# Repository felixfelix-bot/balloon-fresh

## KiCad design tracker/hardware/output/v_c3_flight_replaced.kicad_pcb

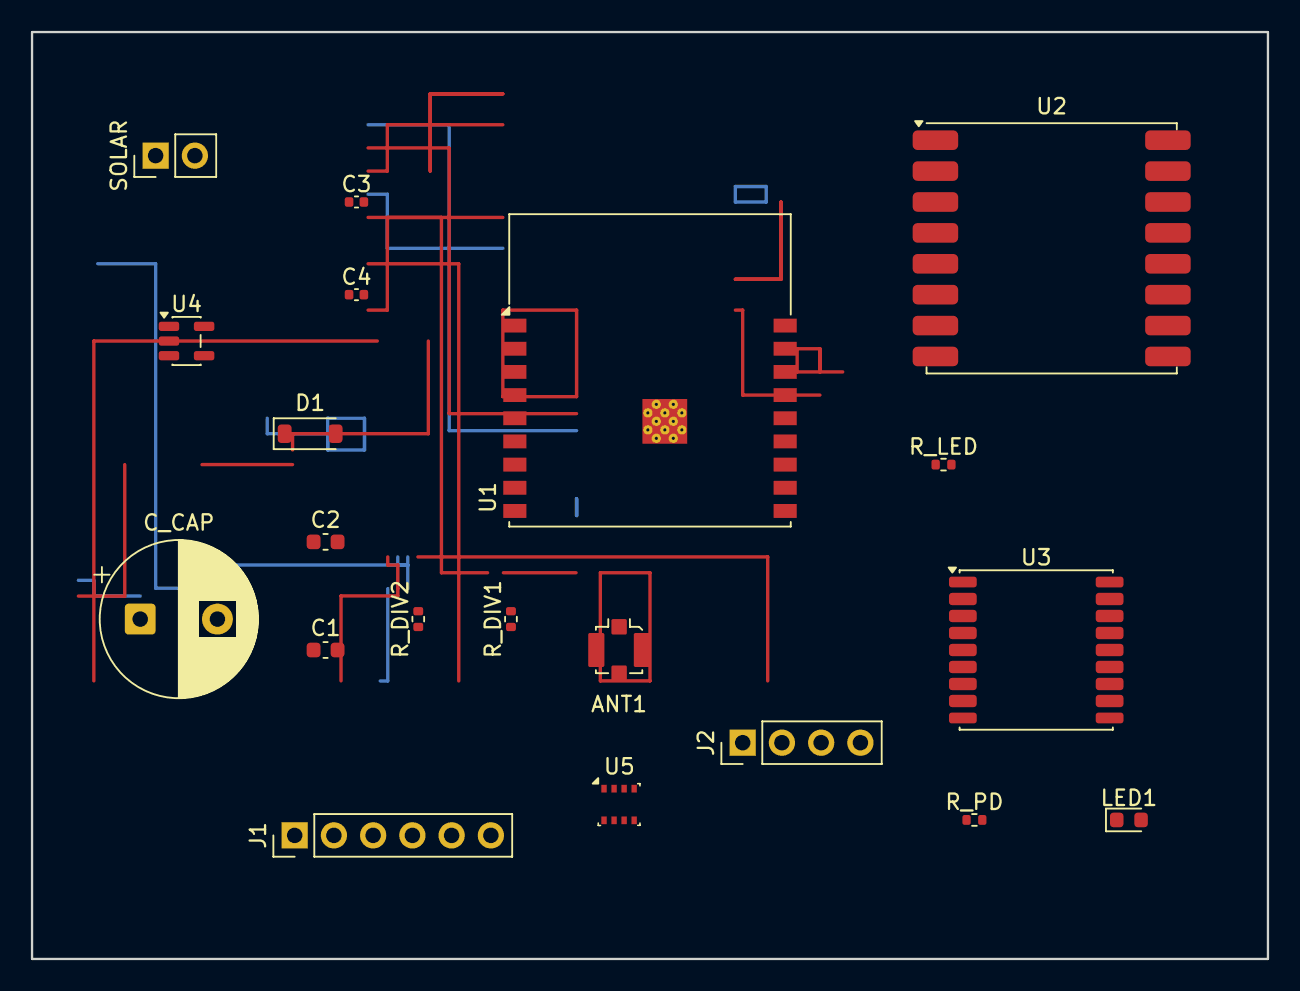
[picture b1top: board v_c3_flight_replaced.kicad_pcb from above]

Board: 4 copper layers, 80.0 x 60.0 mm, 20 parts (0 on the bottom side), 22 nets.

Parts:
ANT1: U.FL; U.FL_Molex_MCRF_73412-0110_Vertical
C1, C2: 10uF; C_0603_1608Metric
C3, C4: 100nF; C_0402_1005Metric
C_CAP: 1F_5.5V; CP_Radial_D10.0mm_P5.00mm
D1: BAT54; D_SOD-123
J1: Prog_Header; PinHeader_1x06_P2.54mm_Vertical
J2: Debug_Header; PinHeader_1x04_P2.54mm_Vertical
LED1: LED_RED; LED_0603_1608Metric
R_DIV1, R_DIV2: 100k; R_0402_1005Metric
R_LED: 330R; R_0402_1005Metric
R_PD: 10k; R_0402_1005Metric
SOLAR: Solar_In; PinHeader_1x02_P2.54mm_Vertical
U1: ESP32-C3-WROOM-02
U2: LR2021F33; HOPERF_RFM9XW_SMD
U3: MAX-M10S; ublox_MAX
U4: TPS7A02; SOT-23-5
U5: BMP280; Bosch_LGA-8_2.5x2.5mm_P0.65mm_ClockwisePinNumbering

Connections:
+3V3: C1.1, C2.1, C3.1, C4.1, J1.2, J2.2, R_PD.2, U1.1, U2.13, U3.7, U3.8, U4.5, U5.2, U5.6, U5.8
EN: J1.3, U1.2
GND: ANT1.2, C1.2, C2.2, C3.2, C4.2, C_CAP.2, J1.1, J2.1, LED1.2, R_DIV2.2, SOLAR.2, U1.9, U1.19, U2.1, U2.8, U2.10, U3.1, U3.10, U3.12, U4.2, U5.1, U5.5, U5.7
GPS_RX: U1.17, U3.2
GPS_TX: U1.18, U3.3
I2C_SCL: J2.4, U1.8, U5.4
I2C_SDA: J2.3, R_PD.1, U1.7, U5.3
LED_A: LED1.1, R_LED.2
LED_DRIVE: R_LED.1, U1.14
LR_BUSY: U1.3, U2.12
LR_DIO0: U1.13, U2.14
LR_RST: U1.15, U2.6
RF_OUT: ANT1.1, U2.9
SOLAR_IN: D1.1, SOLAR.1
SPI_MISO: U1.16, U2.2
SPI_MOSI: U1.6, U2.3
SPI_NSS: U1.10, U2.5
SPI_SCK: U1.5, U2.4
UART0_RX: J1.5, U1.11
UART0_TX: J1.4, U1.12
VCAP: C_CAP.1, D1.2, R_DIV1.1, U4.1
VDIV_MID: R_DIV1.2, R_DIV2.1, U1.4

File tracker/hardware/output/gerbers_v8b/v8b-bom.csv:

Comment,Designator,Footprint,Layer,Qty
U.FL,ANT1,U.FL_Molex_MCRF_73412-0110_Vertical,top,1
10uF,C1,C_0603_1608Metric,top,1
10uF,C2,C_0603_1608Metric,top,1
100nF,C3,C_0402_1005Metric,top,1
100nF,C4,C_0402_1005Metric,top,1
1F_5.5V,C_CAP,CP_Radial_D10.0mm_P5.00mm,top,1
BAT54,D1,D_SOD-123,top,1
Prog_Header,J1,PinHeader_1x06_P2.54mm_Vertical,top,1
Debug_Header,J2,PinHeader_1x04_P2.54mm_Vertical,top,1
LED_RED,LED1,LED_0603_1608Metric,top,1
100k,R_DIV1,R_0402_1005Metric,top,1
100k,R_DIV2,R_0402_1005Metric,top,1
330R,R_LED,R_0402_1005Metric,top,1
10k,R_PD,R_0402_1005Metric,top,1
Solar_In,SOLAR,PinHeader_1x02_P2.54mm_Vertical,top,1
ESP32-C3-WROOM-02,U1,ESP32-C3-WROOM-02,top,1
LR2021F33,U2,HOPERF_RFM9XW_SMD,top,1
MAX-M10S,U3,ublox_MAX,top,1
TPS7A02,U4,SOT-23-5,top,1
BMP280,U5,Bosch_LGA-8_2.5x2.5mm_P0.65mm_ClockwisePinNumbering,top,1

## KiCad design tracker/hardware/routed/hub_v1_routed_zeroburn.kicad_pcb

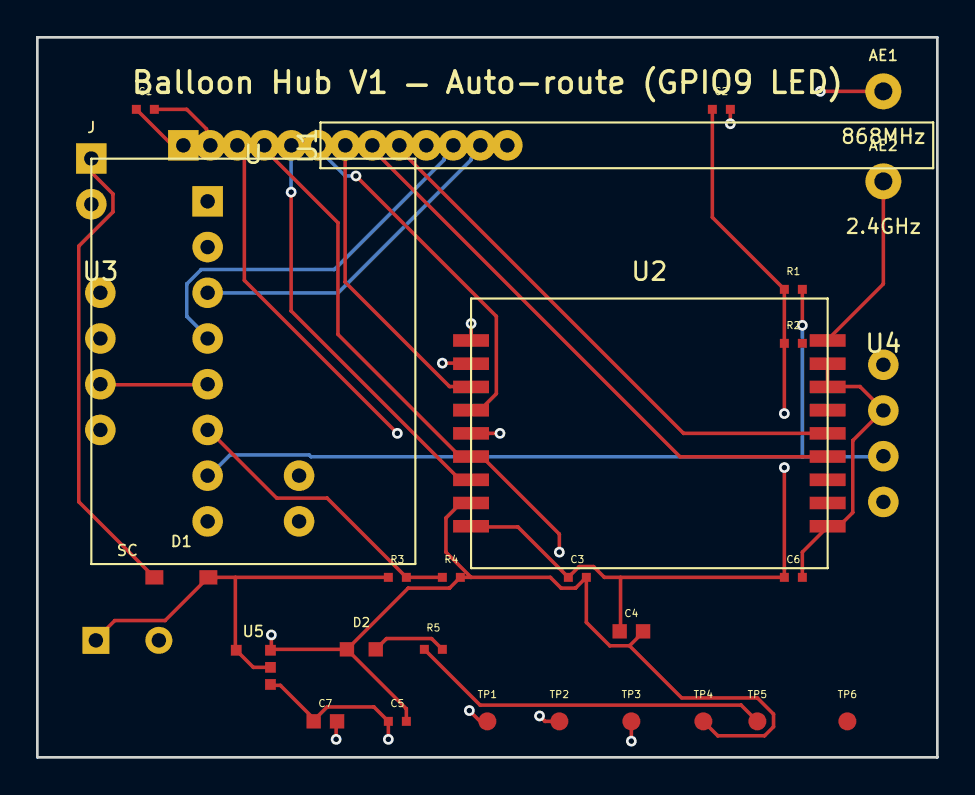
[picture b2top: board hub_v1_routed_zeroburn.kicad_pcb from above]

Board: 4 copper layers, 50.0 x 40.0 mm, 30 parts (0 on the bottom side), 20 nets.

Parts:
AE1: 868MHz; TestPoint_THTPad_D2.0mm_Drill1.0mm
AE2: 2.4GHz; TestPoint_THTPad_D2.0mm_Drill1.0mm
C1, C2, C3, C5, C6: 100nF; C_0402_1005Metric
C4, C7: 10uF; C_0805_2012Metric
D1: BAT54; D_SOD-123
D2: STATUS; LED_0603_1608Metric
J: SOLAR; PinHeader_1x02_P2.54mm_Vertical
R1, R2: 4.7k; R_0402_1005Metric
R3, R4: 1M; R_0402_1005Metric
R5: 330R; R_0402_1005Metric
SC: 1F 5.5V; CP_Radial_D8.0mm_P3.50mm
TP1: SPI0_SCK; TestPoint_Pad_D1.0mm
TP2: SPI0_MOSI; TestPoint_Pad_D1.0mm
TP3: 3V3; TestPoint_Pad_D1.0mm
TP4: GND; TestPoint_Pad_D1.0mm
TP5: LED_GPIO18; TestPoint_Pad_D1.0mm
TP6: FEM_TX_GPIO19; TestPoint_Pad_D1.0mm
U: ESP32-C3-Mini-1; ESP32-C3_Mini_V1_Header
U1: RP2040-Zero; PinHeader_1x13_P2.54mm_Vertical
U2: LoRa2021; LoRa2021_Castellated
U3: MAX-M10S; PinHeader_1x04_P2.54mm_Vertical
U4: MS5611; PinHeader_1x04_P2.54mm_Vertical
U5: TPS7A02; SOT-23-5

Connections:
3V3: C1.1, C2.1, C3.1, C4.1, C5.1, C6.1, C7.1, R1.1, R2.1, TP3.1, U.1, U1.1, U2.1, U3.1, U4.1, U5.5
ESP_TX_RP2040_RX: U.3, U1.12
GND: C1.2, C2.2, C3.2, C4.2, C5.2, C6.2, C7.2, D2.1, J.2, R4.2, SC.2, TP4.1, U.2, U1.2, U1.13, U2.2, U2.8, U2.11, U2.12, U2.18, U3.2, U4.2, U5.2
GPS_TX_ESP_RX: U.5, U3.3
I2C_SDA: R1.2, U.7, U4.3
LED_ANODE: D2.2, R5.2
LR2021_BUSY: U1.7, U2.7
LR2021_DIO9: U1.8, U2.15
LR2021_RST: U1.9, U2.14
RF_2G4_2400: AE2.1, U2.10
RF_SUB_868: AE1.1, U2.9
RP2040_TX_ESP_RX: U.4, U1.11
SOLAR_IN: D1.1, J.1
SPI0_MISO: U1.5, U2.3
SPI0_MOSI: TP2.1, U1.4, U2.4
SPI0_NSS: U1.6, U2.6
SPI0_SCK: TP1.1, U1.3, U2.5
STATUS_LED: R5.1, TP5.1
VCAP: D1.2, R3.1, SC.1, U5.1, U5.3
VDIV_MID: R3.2, R4.1, U.6
